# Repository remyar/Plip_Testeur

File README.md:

# Plip_Testeur
Testeur de clef Plip IR PSA

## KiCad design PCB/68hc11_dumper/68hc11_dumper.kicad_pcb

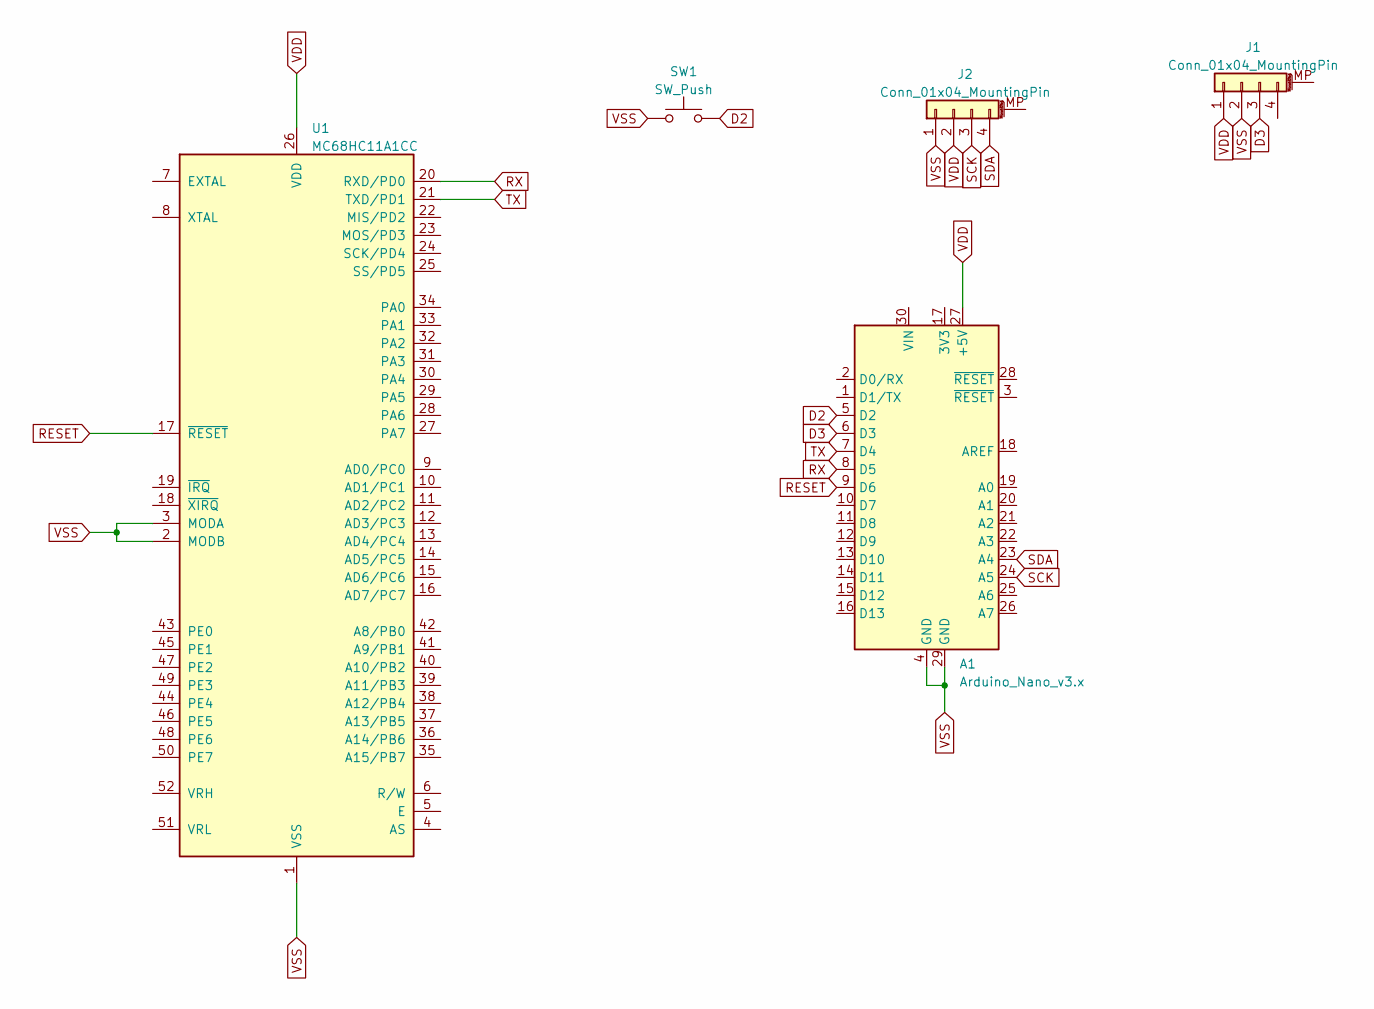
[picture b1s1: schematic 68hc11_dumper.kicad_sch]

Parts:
A1: Arduino_Nano_v3.x; Arduino_Nano
J1, J2: Conn_01x04_MountingPin; PinSocket_1x04_P2.54mm_Vertical
SW1: SW_Push; SW_PUSH_6mm
U1: MC68HC11A1CC; PLCC-52_THT-Socket

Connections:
D2: A1.5 (D2), SW1.2
D3: A1.6 (D3), J1.3
RESET: A1.9 (D6), U1.17 (~RESET)
RX: A1.8 (D5), U1.20 (RXD/PD0)
SCK: A1.24 (A5), J2.3
SDA: A1.23 (A4), J2.4
TX: A1.7 (D4), U1.21 (TXD/PD1)
VDD: A1.27 (+5V), J1.1, J2.2, U1.26 (VDD)
VSS: A1.4 (GND), A1.29 (GND), J1.2, J2.1, SW1.1, U1.1 (VSS), U1.2 (MODB), U1.3 (MODA)

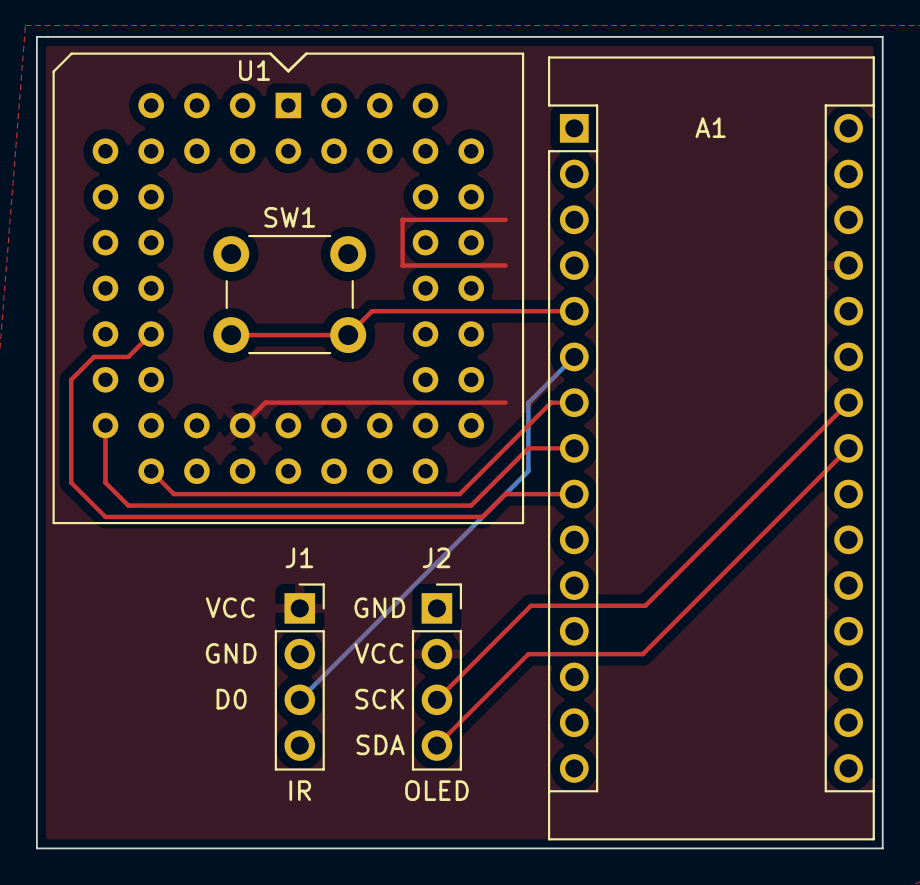
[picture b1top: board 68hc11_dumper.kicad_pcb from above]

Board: 2 copper layers, 47.0 x 45.1 mm, 5 parts (0 on the bottom side), 9 nets.

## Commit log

2021-12-09 azdd
2021-12-10 add lcd
2021-12-10 dffd
2024-12-04 add doc
